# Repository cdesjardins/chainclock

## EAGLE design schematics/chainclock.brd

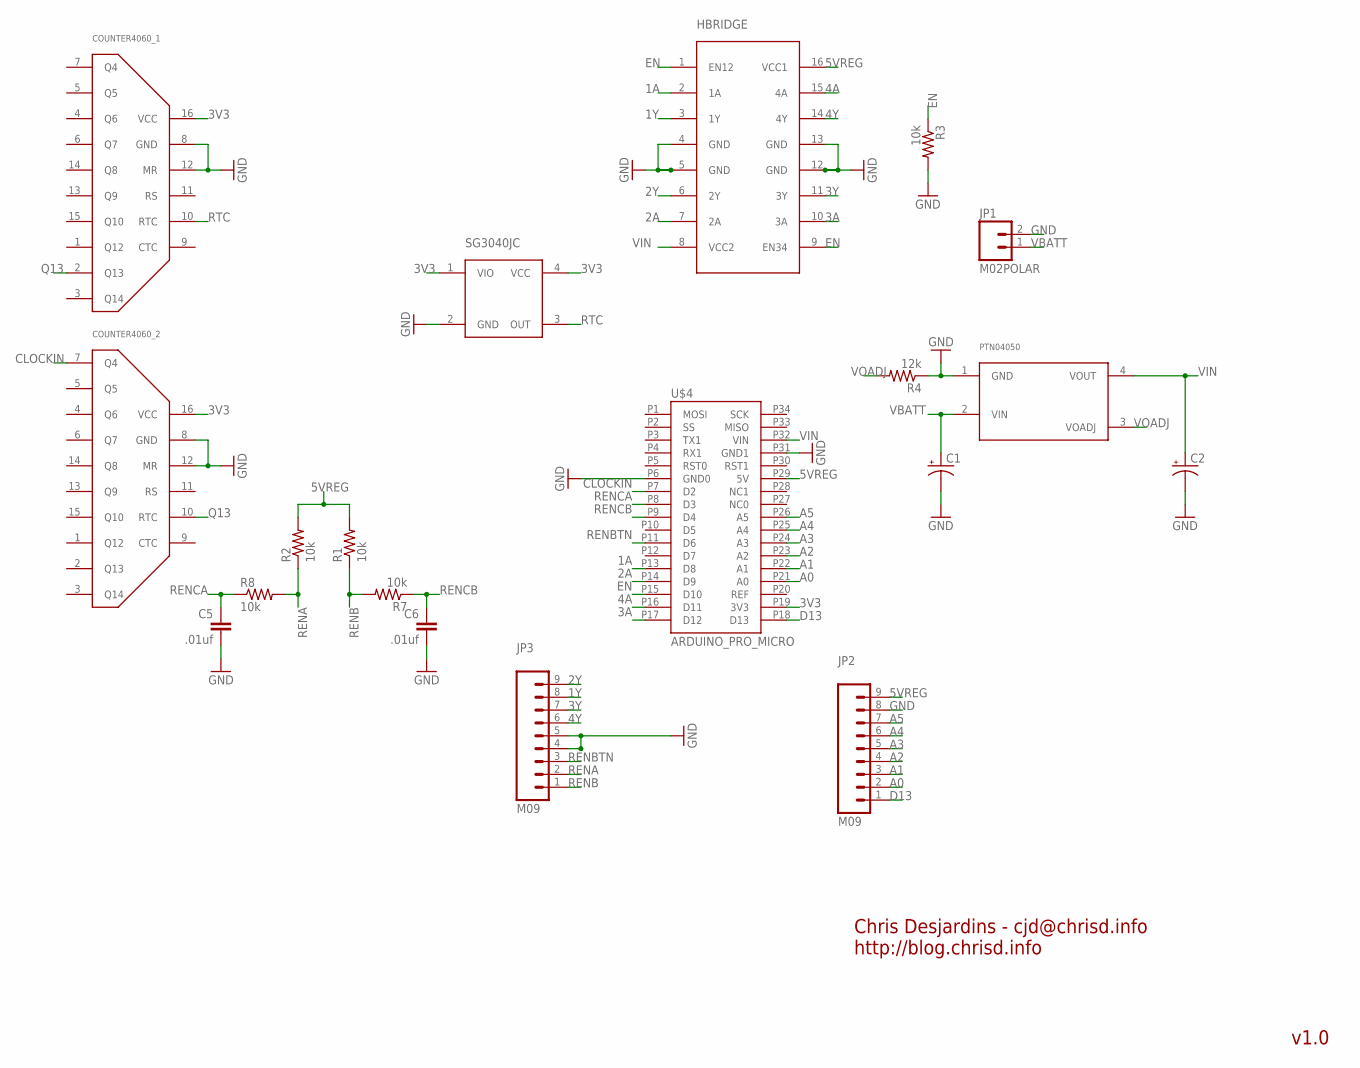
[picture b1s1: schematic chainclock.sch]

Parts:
C1, C2: CAP_POLPTH1; CPOL-RADIAL-100UF-25V
C5, C6: .01uf; CAP-PTH-SMALL-KIT
COUNTER4060_1, COUNTER4060_2: 4060SOIC16; SO016
HBRIDGE: SN754410; DIL16-KIT
JP1: M02POLAR; MOLEX-1X2
JP2, JP3: M09; 1X09
PTN04050: PTN0405C; EUU4
R1, R2, R3, R7, R8: 10k; AXIAL-0.3EZ
R4: 12k; AXIAL-0.3EZ
SG3040JC: SG30XXJC; SG3030JC
U$4: ARDUINO_PRO_MICRO

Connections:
1A: HBRIDGE.2 (1A), U$4.P13 (D8)
1Y: HBRIDGE.3 (1Y), JP3.8
2A: HBRIDGE.7 (2A), U$4.P14 (D9)
2Y: HBRIDGE.6 (2Y), JP3.9
3A: HBRIDGE.10 (3A), U$4.P17 (D12)
3V3: COUNTER4060_1.16 (VCC), COUNTER4060_2.16 (VCC), SG3040JC.1 (VIO), SG3040JC.4 (VCC), U$4.P19 (3V3)
3Y: HBRIDGE.11 (3Y), JP3.7
4A: HBRIDGE.15 (4A), U$4.P16 (D11)
4Y: HBRIDGE.14 (4Y), JP3.6
5VREG: HBRIDGE.16 (VCC1), JP2.9, R1.P$2 (2), R2.P$2 (2), U$4.P29 (5V)
A0: JP2.2, U$4.P21 (A0)
A1: JP2.3, U$4.P22 (A1)
A2: JP2.4, U$4.P23 (A2)
A3: JP2.5, U$4.P24 (A3)
A4: JP2.6, U$4.P25 (A4)
A5: JP2.7, U$4.P26 (A5)
CLOCKIN: COUNTER4060_2.7 (Q4), U$4.P7 (D2)
D13: JP2.1, U$4.P18 (D13)
EN: HBRIDGE.1 (EN12), HBRIDGE.9 (EN34), R3.P$1 (1), U$4.P15 (D10)
GND: C1.2 (-), C2.2 (-), C5.2, C6.2, COUNTER4060_1.8 (GND), COUNTER4060_1.12 (MR), COUNTER4060_2.8 (GND), COUNTER4060_2.12 (MR), HBRIDGE.4 (GND), HBRIDGE.5 (GND), HBRIDGE.12 (GND), HBRIDGE.13 (GND), JP1.2, JP2.8, JP3.4, JP3.5, PTN04050.1 (GND), R3.P$2 (2), R4.P$1 (1), SG3040JC.2 (GND), U$4.P6 (GND0), U$4.P31 (GND1)
Q13: COUNTER4060_1.2 (Q13), COUNTER4060_2.10 (RTC)
REF: U$4.P20 (REF)
RENA: JP3.2, R2.P$1 (1), R8.P$2 (2)
RENB: JP3.1, R1.P$1 (1), R7.P$2 (2)
RENBTN: JP3.3, U$4.P11 (D6)
RENCA: C5.1, R8.P$1 (1), U$4.P8 (D3)
RENCB: C6.1, R7.P$1 (1), U$4.P9 (D4)
RTC: COUNTER4060_1.10 (RTC), SG3040JC.3 (OUT)
VBATT: C1.1 (+), JP1.1, PTN04050.2 (VIN)
VIN: C2.1 (+), HBRIDGE.8 (VCC2), PTN04050.4 (VOUT), U$4.P32 (VIN)
VOADJ: PTN04050.3 (VOADJ), R4.P$2 (2)

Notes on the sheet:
Chris Desjardins - cjd@chrisd.info http://blog.chrisd.info
v1.0

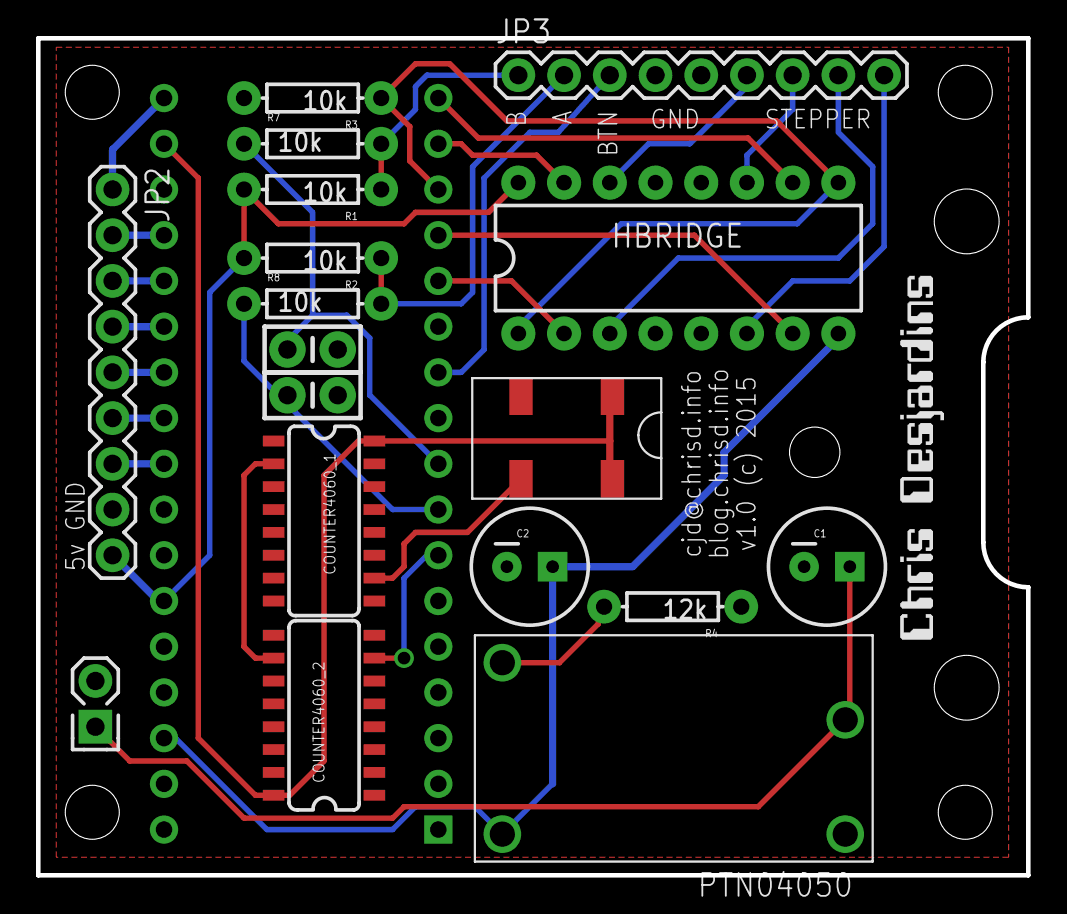
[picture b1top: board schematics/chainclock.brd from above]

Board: 2 copper layers, 55.0 x 46.5 mm, 21 parts (0 on the bottom side), 30 nets.

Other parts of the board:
U$2: NEMA14
U$3: LOGO

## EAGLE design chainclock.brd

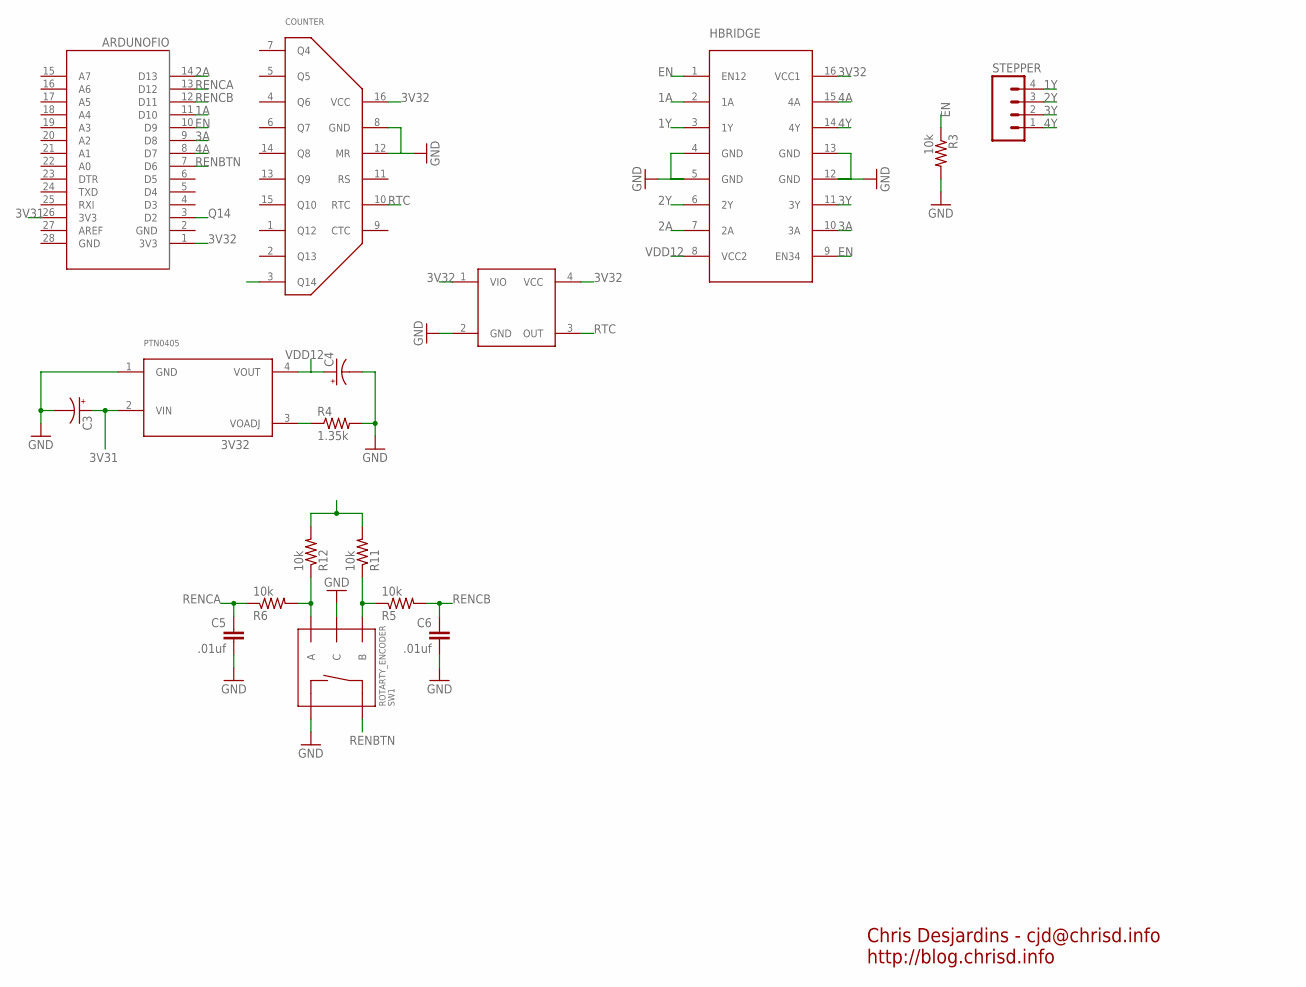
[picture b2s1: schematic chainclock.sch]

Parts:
ARDUNOFIO: ARDUINOFIO
C3, C4: CAP_POLPTH1; CPOL-RADIAL-100UF-25V
C5, C6: .01uf; CAP-PTH-SMALL-KIT
COUNTER: 4060; DIL16-KIT
HBRIDGE: SN754410; DIL16-KIT
PTN0405: PTN0405C; EUU4
R3: 10k; AXIAL-0.3EZ
R4: 1.35k; AXIAL-0.3EZ
R5, R6, R11, R12: 10k; R2010
STEPPER: M04PTH; 1X04
SW1: ROTARTY_ENCODER; ROTARY_ENC_PLAIN
U$4: SG30XXJC; SG3030JC

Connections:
1A: ARDUNOFIO.11 (D10), HBRIDGE.2 (1A)
1Y: HBRIDGE.3 (1Y), STEPPER.4
2A: ARDUNOFIO.14 (D13), HBRIDGE.7 (2A)
2Y: HBRIDGE.6 (2Y), STEPPER.3
3A: ARDUNOFIO.9 (D8), HBRIDGE.10 (3A)
3V31: ARDUNOFIO.26 (3V3), C3.1 (+), PTN0405.2 (VIN)
3V32: ARDUNOFIO.1 (3V3), COUNTER.16 (VCC), HBRIDGE.16 (VCC1), R11.2, R12.2, U$4.1 (VIO), U$4.4 (VCC)
3Y: HBRIDGE.11 (3Y), STEPPER.2
4A: ARDUNOFIO.8 (D7), HBRIDGE.15 (4A)
4Y: HBRIDGE.14 (4Y), STEPPER.1
EN: ARDUNOFIO.10 (D9), HBRIDGE.1 (EN12), HBRIDGE.9 (EN34), R3.P$1 (1)
GND: ARDUNOFIO.2 (GND), ARDUNOFIO.28 (GND), C3.2 (-), C4.2 (-), C5.2, C6.2, COUNTER.8 (GND), COUNTER.12 (MR), HBRIDGE.4 (GND), HBRIDGE.5 (GND), HBRIDGE.12 (GND), HBRIDGE.13 (GND), PTN0405.1 (GND), R3.P$2 (2), R4.P$2 (2), SW1.C, SW1.SW-, U$4.2 (GND)
unnamed: R5.1, R11.1, SW1.B
unnamed: PTN0405.3 (VOADJ), R4.P$1 (1)
unnamed: R6.2, R12.1, SW1.A
Q14: ARDUNOFIO.3 (D2), COUNTER.3 (Q14)
RENBTN: ARDUNOFIO.7 (D6), SW1.SW+
RENCA: ARDUNOFIO.13 (D12), C5.1, R6.1
RENCB: ARDUNOFIO.12 (D11), C6.1, R5.2
RTC: COUNTER.10 (RTC), U$4.3 (OUT)
VDD12: C4.1 (+), HBRIDGE.8 (VCC2), PTN0405.4 (VOUT)

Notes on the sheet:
Chris Desjardins - cjd@chrisd.info http://blog.chrisd.info

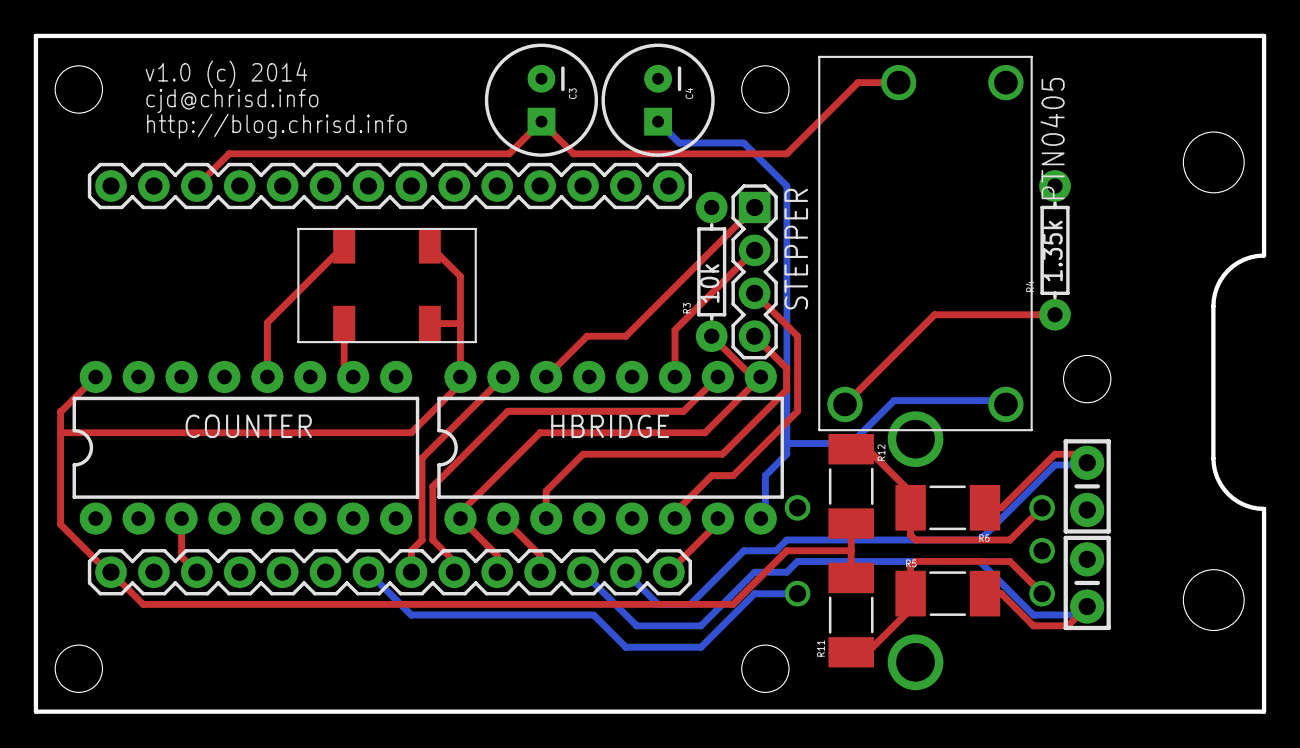
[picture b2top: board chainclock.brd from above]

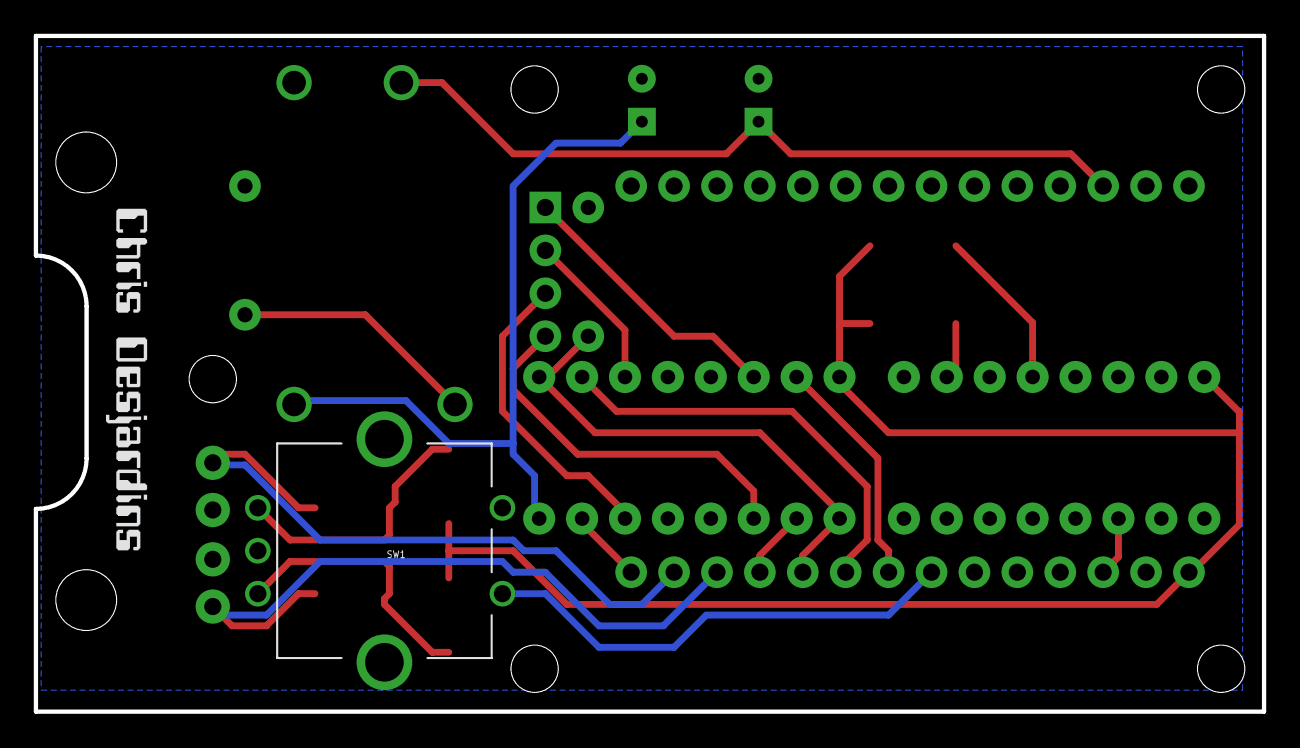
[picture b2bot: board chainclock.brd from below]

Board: 2 copper layers, 72.7 x 40.0 mm, 19 parts (2 on the bottom side), 21 nets.

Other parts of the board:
U$2: NEMA14
U$3: LOGO

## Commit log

2014-03-16 Updates to chainclock, adding motor
2014-03-17 Move some stuff around
2014-03-17 Add logo
2014-03-17 Move around voltage reg
2014-03-18 Switch out crystal
2014-03-18 rework layout
2014-03-20 Small updates
2014-03-21 Add clockface
2014-03-22 Update clock face
2014-03-23 Update layout
2014-03-23 Adding clockface and sprocket holder thing
2014-03-23 Adding solar holder thing
2014-03-23 New board layout
2014-03-23 Center motor
2014-03-25 Add voltage limiter for solar
2014-03-29 Updates to the counter
2014-03-30 Updated to use 2 4060 and...
2014-03-30 Move power header
2014-03-31 Use int line for rot enc
2014-03-31 Move encoder off board
2014-04-09 Updates to chainlock
2014-04-26 Originize the routin
2014-05-03 Update layout of chainclock
2015-11-10 First pass
2015-11-22 Start on software and v2.0
2015-11-24 Update chainclock code
2015-11-24 Add rotary encoder support
2015-11-24 Add button support
2015-11-24 Tweak the rotary encoder
2015-11-24 Fix bug
2015-12-06 Add new frame for holding everything together

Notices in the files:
chainclock.brd:
v1.0 (c) 2014
schematics/chainclock.brd:
v1.0 (c) 2015
parts and their libraries:
SparkFun-Resistors: Licensing: Creative Commons ShareAlike 4.0 International - https://creativecommons.org/licenses/by-sa/4.0
